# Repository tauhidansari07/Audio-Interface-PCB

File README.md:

# Custom Bluetooth Audio Interface PCB

A custom printed circuit board designed to integrate a Bluetooth converting into 3.5mm jack for devices that doesnt have one and you wanna connect your fav wired earphones or headsets 

## Technical Details
* **Core IC:** FM9688 (Power Management / Buck Converter), FSC-BT1026E (blutooth receiver)
* **Design Software:** KiCad 
* **Key Features:** To Get Audio Output For 3.5mm Jack Through Blutooth Low Letency For Gaming Purpose or General Purpose

## Included Files
* KiCad source files (Schematic & PCB layout)
* PDF Schematic for quick viewing
* Ready-to-manufacture Gerber files

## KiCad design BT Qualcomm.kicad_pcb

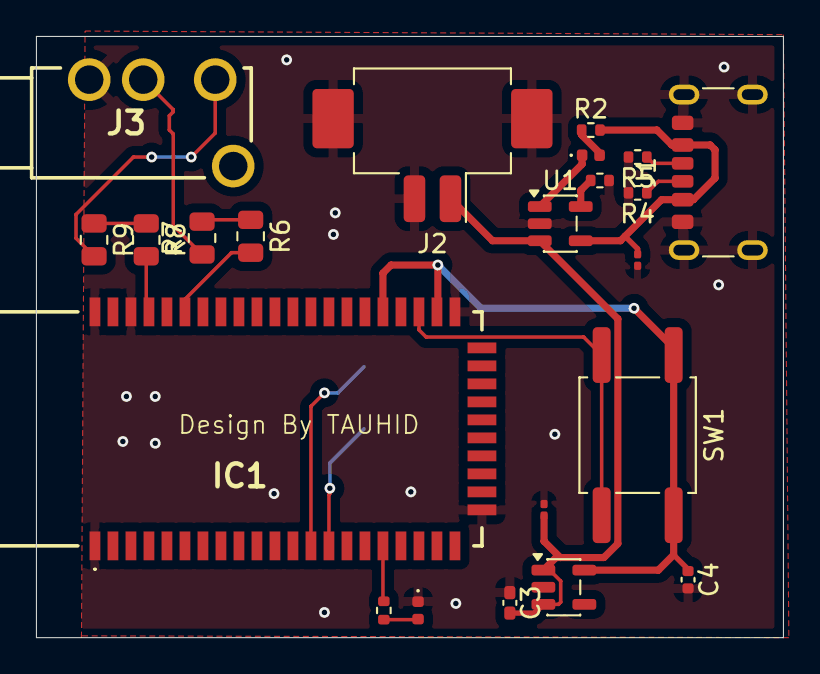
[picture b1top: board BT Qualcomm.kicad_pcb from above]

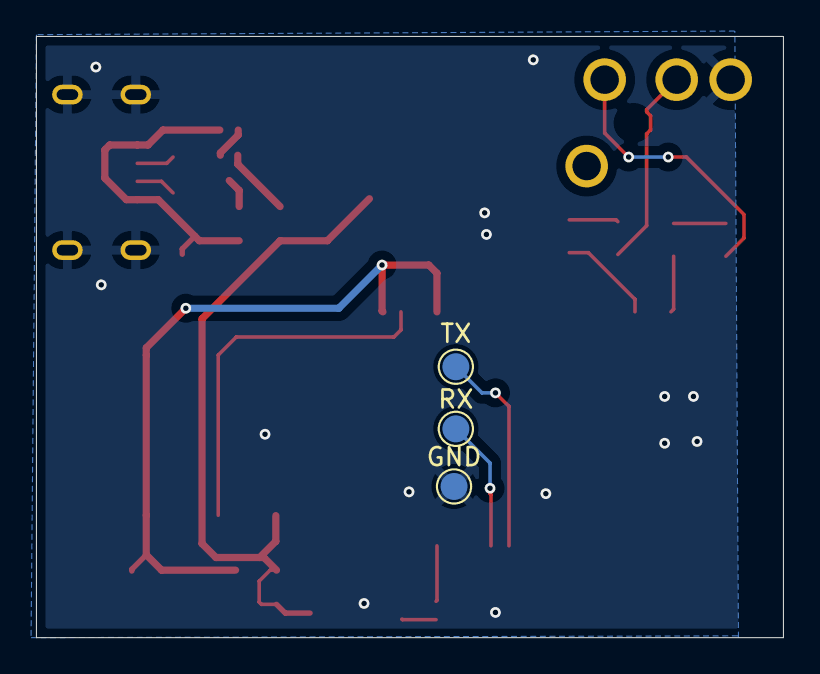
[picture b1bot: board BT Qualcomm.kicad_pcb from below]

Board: 2 copper layers, 41.5 x 33.4 mm, 25 parts (3 on the bottom side), 20 nets.

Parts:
C1, C2: 4.7uF; C_0201_0603Metric
C3: 1uF; C_0402_1005Metric_Pad0.74x0.62mm_HandSolder
C4: 1uF; C_0402_1005Metric
D1, D2: LED; LED_0402_1005Metric
GND: GND; TestPoint_Pad_D1.5mm
IC1: FSC-BT1026E; FSCBT1026E
J1: USB_C_Receptacle_PowerOnly_6P; USB_C_Receptacle_GCT_USB4125-xx-x-0190_6P_TopMnt_Horizontal
J2: Battery CON; Hirose_DF3EA-02P-2V_1x02-1MP_P2.00mm_Vertical
J3: PJ-320A; PJ320A
R1: 10K; R_0402_1005Metric
R2: 1k; R_0402_1005Metric
R3: 330Ω; R_0402_1005Metric
R4, R5: 5.1K; R_0402_1005Metric
R6, R7, R8, R9: 47uF; R_0805_2012Metric
RX: RX; TestPoint_Pad_D1.5mm
SW1: SW_Push; SW_Push_1P1T_NO_CK_KSC6xxG
TX: TX; TestPoint_Pad_D1.5mm
U1: MCP73831-2-OT; SOT-23-5
U2: AP2112K-3.3; SOT-23-5

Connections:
GND: C1.2, C2.1, C3.1, C4.2, D2.1 (K), GND.1, IC1.1 (GND_1), IC1.22 (GND_2), IC1.32 (GND_3), IC1.50 (GND_4), IC1.52 (GND_5), J1.A12 (GND), J1.B12 (GND), J1.S1 (SHIELD), J2.2 (GND), J2.MP (MountPin), J3.2 (GND), R1.2, R4.2, R5.2, U1.2 (V_{SS}), U2.2 (GND)
unnamed: D1.2 (A), R2.1
unnamed: D1.1 (K), U1.1 (STAT)
unnamed: D2.2 (A), R3.1
unnamed: IC1.14 (BT_RX/PIO4), RX.2 (RX)
unnamed: IC1.13 (BT_TX/PIO5), TX.1 (TX)
unnamed: IC1.17 (LED0/AIO0), R3.2
unnamed: IC1.49 (SPK_LP), R8.2
unnamed: IC1.47 (SPK_RP), R6.2
unnamed: IC1.34 (SYS_CTRL), SW1.1
unnamed: C4.1, IC1.33 (VBAT_IN), IC1.36 (VDD_IO), SW1.2, U2.5 (VOUT)
unnamed: J1.A5 (CC1), R4.1
unnamed: J1.B5 (CC2), R5.1
unnamed: C2.2, C3.2, J2.1 (VBAT), U1.3 (V_{BAT}), U2.1 (VIN), U2.3 (EN)
unnamed: J3.4 (LEFT), R9.2
unnamed: J3.3 (RIGHT), R7.1
unnamed: R6.1, R7.2
unnamed: R8.1, R9.1
unnamed: R1.1, U1.5 (PROG)
unnamed: C1.1, J1.A9 (VBUS), J1.B9 (VBUS), R2.2, U1.4 (V_{DD})

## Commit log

2026-05-17 Rename pdf print sch.pdf to Schematic.pdf
